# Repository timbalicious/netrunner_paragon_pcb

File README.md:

# netrunner_paragon_pcb
Possibly functional PCB alt-art Paragon for the Netrunner LCG

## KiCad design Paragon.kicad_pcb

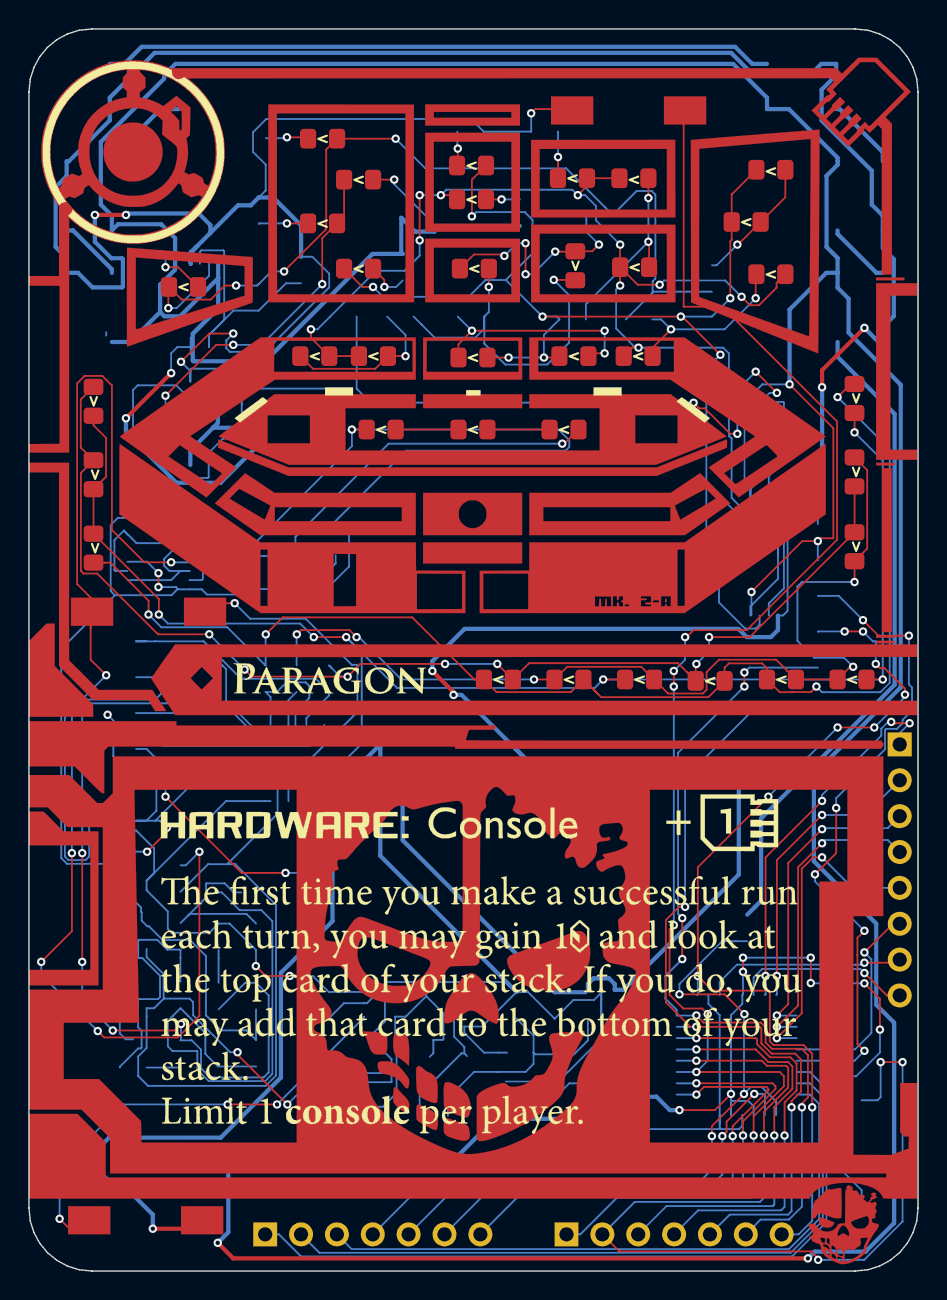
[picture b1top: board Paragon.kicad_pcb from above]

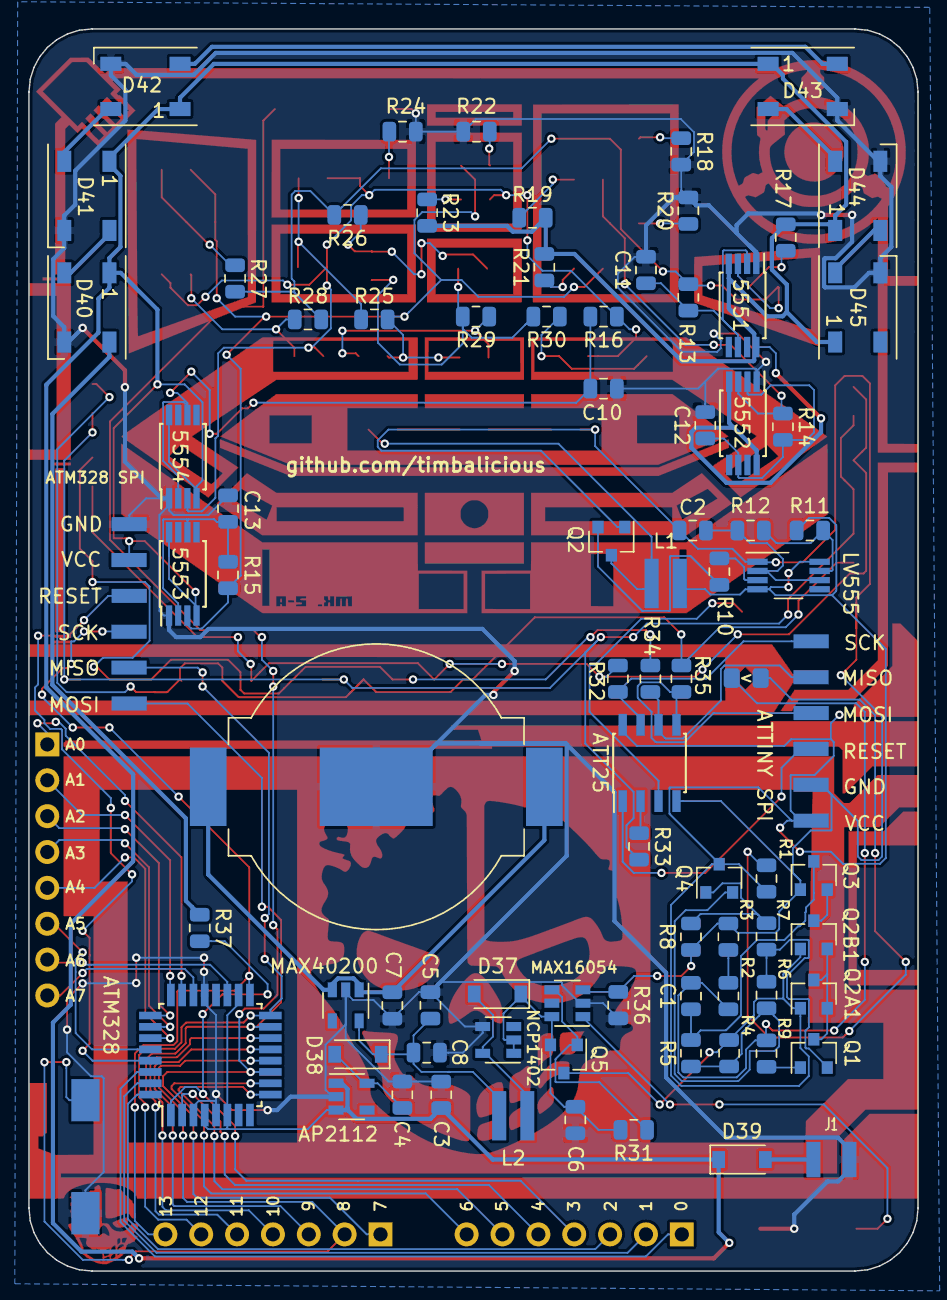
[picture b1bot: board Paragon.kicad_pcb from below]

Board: 2 copper layers, 63.0 x 88.0 mm, 125 parts (87 on the bottom side), 91 nets.

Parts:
5551, 5552, 5553, 5554: NE555; TSSOP-8_4.4x3mm_P0.65mm
AP2112: AP2112K-3.3; SOT-23-5
ATA1: Conn_01x08_Male; PinHeader_1x08_P2.54mm_Vertical
ATD1, ATD2: Conn_01x07_Male; PinHeader_1x07_P2.54mm_Vertical
ATM328: ATmega328P-AU; TQFP-32_7x7mm_P0.8mm
ATM328 SPI: Conn_01x06_Female; ConnectorMicromatch-12
ATT25: ATtiny25V-10SU; SOIC-8_3.9x4.9mm_P1.27mm
ATTINY SPI: Conn_01x06_Female; ConnectorMicromatch-12
BT1: Battery 1.5 - 3V; BatteryHolder_MPD_BC2003_1x2032
C1: CP1; C_0805_2012Metric
C2: 470pF; C_0805_2012Metric
C3, C4: 1uf; C_0805_2012Metric
C5, C10, C11, C12, C13: 10uf; C_0805_2012Metric
C6: 68uf; C_0805_2012Metric
C7, C8: 33uf; C_0805_2012Metric
D1, D2, D3, D4, D5, D6, D7, D8, D9, D10, D11, D12, D13, D14, D15, D16, D17, D18, D19, D20, D21, D22, D23, D24, D25, D26, D27, D28, D29, D30, D31, D32, D33, D34, D35, D36: LED; LED_0805_cardfront
D37, D38, D39: MBR0520LT; D_SOD-123
D40, D41, D42, D43, D44, D45: WS2812B; LED_WS2812B_PLCC4_5.0x5.0mm_P3.2mm
J1: Conn_01x02_Male; Connector_2.54_2pin_SMD
L1: L; CD32_coil
L2: 47uh; CD32_coil
LV555: ICM7555; VSSOP-8_3.0x3.0mm_P0.65mm
MAX16054: MAX16054; SOT-23-6
MAX40200: MAX40200; SOT-23-5
NCP1402: NCP1402; SOT-23-5
Q1, Q3, Q4: 2N3904; SOT-23
Q2: 2N2222; SOT-23
Q2A1, Q2B1: 2N3906; SOT-23
Q5: Si2301; SOT-23
R1: 12; R_0805_2012Metric
R2: 5.6K; R_0805_2012Metric
R3: 3.3k; R_0805_2012Metric
R4, R5: 410; R_0805_2012Metric
R6, R8: 22K; R_0805_2012Metric
R7, R12: 10K; R_0805_2012Metric
R9: 100; R_0805_2012Metric
R10, R11: 1K; R_0805_2012Metric
R13: 75k; R_0805_2012Metric
R14: 68K; R_0805_2012Metric
R15: 62k; R_0805_2012Metric
R16: 56k; R_0805_2012Metric
R17, R18, R19, R20, R21, R22, R23, R24, R25, R26, R27, R28, R29, R30: 200; R_0805_2012Metric
R31, R36: 100k; R_0805_2012Metric
R32, R33, R34, R35: 33; R_0805_2012Metric
R37: 220k; R_0805_2012Metric
SW1, SW2, SW3, SW4: SW_Push; SMD_button

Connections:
Earth: 5551.1, 5552.1, 5553.1, 5554.1, AP2112.2, ATM328.3, ATM328.5, ATM328.21, ATM328 SPI.6, BT1.2, C3.2, C4.2, C5.2, C6.2, C7.2, C8.2, C10.2, C11.2, C12.2, C13.2, D40.3, D41.3, D42.3, D43.3, D44.3, D45.3, J1.2, MAX16054.2, MAX40200.2, NCP1402.4, R18.2, R20.2, R22.2, R24.2, R36.2, SW1.1, SW3.2, SW4.2
unnamed: 5551.4, 5551.8, 5552.4, 5552.8, 5553.4, 5553.8, 5554.4, 5554.8, AP2112.1, AP2112.3, ATM328.4, ATM328.6, ATM328.18, ATM328 SPI.5, C3.1, D39.1, D40.1, D41.1, D42.1, D43.1, D44.1, D45.1, R17.2, R19.2, R21.2, R23.2
unnamed: AP2112.5, C4.1, D38.2
unnamed: ATA1.1, ATM328.23
unnamed: ATA1.2, ATM328.24
unnamed: ATA1.3, ATM328.25
unnamed: ATA1.4, ATM328.26
unnamed: ATA1.5, ATM328.27
unnamed: ATA1.6, ATM328.28
unnamed: ATA1.7, ATM328.19
unnamed: ATA1.8, ATM328.22
unnamed: ATD1.1, ATM328.30
unnamed: ATD1.2, ATM328.31
unnamed: ATD1.3, ATM328.32
unnamed: ATD1.4, ATM328.1, R37.2
unnamed: ATD1.5, ATM328.2
unnamed: ATD1.6, ATM328.9
unnamed: ATD1.7, ATM328.10
unnamed: ATD2.1, ATM328.11, SW4.1
unnamed: ATD2.2, ATM328.12, SW3.1
unnamed: ATD2.3, ATM328.13
unnamed: ATD2.4, ATM328.14
unnamed: ATD2.5, ATM328.15, ATM328 SPI.1
unnamed: ATD2.6, ATM328.16, ATM328 SPI.2
unnamed: ATD2.7, ATM328.17, ATM328 SPI.3
unnamed: ATM328.29, ATM328 SPI.4
unnamed: ATT25.1, ATTINY SPI.3
unnamed: ATT25.2, R33.1
unnamed: ATT25.3, SW2.2
unnamed: ATT25.4, ATTINY SPI.2, C2.2, D4.1, LV555.1, MAX16054.3, Q2.1, Q3.1, R3.2, R8.2, R36.1, SW2.1
unnamed: ATT25.5, ATTINY SPI.4, R35.1
unnamed: ATT25.6, ATTINY SPI.5, R34.1
unnamed: ATT25.7, ATTINY SPI.6, R32.1
unnamed: ATT25.8, ATTINY SPI.1, L1.2, LV555.4, LV555.8, Q2A1.1, Q2B1.1, Q4.3, Q5.3, R1.1, R4.1, R11.1
unnamed: BT1.1, C7.1, MAX40200.1, MAX40200.3
unnamed: C1.1, Q3.3, R5.2
unnamed: C1.2, D1.1, R2.1, R9.2
unnamed: C2.1, LV555.2, LV555.6, R12.2
unnamed: C5.1, C8.1, D38.1, L2.1, MAX40200.5
unnamed: C6.1, D37.1, MAX16054.6, NCP1402.1, NCP1402.2, Q5.2, R31.2
unnamed: 5554.2, 5554.6, C10.1, R16.2
unnamed: 5551.2, 5551.6, C11.1, R13.2
unnamed: 5552.2, 5552.6, C12.1, R14.2
unnamed: 5553.2, 5553.6, C13.1, R15.2
unnamed: D1.2, R1.2
unnamed: D2.1, D3.2
unnamed: D2.2, L1.1, Q2.3
unnamed: D3.1, D4.2
unnamed: 5551.3, D5.1, D6.2, R13.1, R26.2, R27.2, R28.2
unnamed: D5.2, R17.1
unnamed: D6.1, R18.1
unnamed: 5552.3, D7.1, D8.2, R14.1
unnamed: D7.2, R19.1
unnamed: D8.1, R20.1
unnamed: D9.2, R21.1
unnamed: D10.1, R22.1
unnamed: 5553.3, D9.1, D10.2, D17.2, D18.1, D21.2, D22.1, R15.1, R25.2
unnamed: 5554.3, D11.1, D12.2, D13.2, D14.1, D19.2, D20.1, D23.2, D24.1, R16.1
unnamed: D11.2, R23.1
unnamed: D12.1, R24.1
unnamed: D13.1, D14.2, R25.1
unnamed: D15.1, D16.2, R26.1
unnamed: D15.2, D16.1, R29.2, R30.2
unnamed: D17.1, D18.2, R27.1
unnamed: D19.1, D20.2, R28.1
unnamed: D21.1, D22.2, R29.1
unnamed: D23.1, D24.2, R30.1
unnamed: D25.1, D26.2, D28.2, D29.1, D31.2, D32.1, R34.2
unnamed: D25.2, D28.1, D33.2, D34.1, D35.2, D36.1, R33.2
unnamed: D26.1, D27.2, D29.2, D30.1, D33.1, D34.2, R35.2
unnamed: D27.1, D30.2, D31.1, D32.2, D35.1, D36.2, R32.2
unnamed: D37.2, L2.2, NCP1402.5
unnamed: D39.2, J1.1
unnamed: D40.2, D41.4
unnamed: D40.4, R37.1
unnamed: D41.2, D42.4
unnamed: D42.2, D43.4
unnamed: D43.2, D44.4
unnamed: D44.2, D45.4
unnamed: LV555.3, R10.2
unnamed: LV555.7, R11.2, R12.1
unnamed: MAX16054.1, SW1.2
unnamed: MAX16054.4, Q5.1, R31.1
unnamed: Q1.1, R9.1
unnamed: Q1.2, R6.2, R7.1
unnamed: Q1.3, Q2A1.2, Q2A1.3, Q2B1.2
unnamed: Q2.2, R10.1
unnamed: Q2B1.3, Q3.2
unnamed: Q4.1, R7.2, R8.1
unnamed: Q4.2, R4.2, R5.1, R6.1
unnamed: R2.2, R3.1
